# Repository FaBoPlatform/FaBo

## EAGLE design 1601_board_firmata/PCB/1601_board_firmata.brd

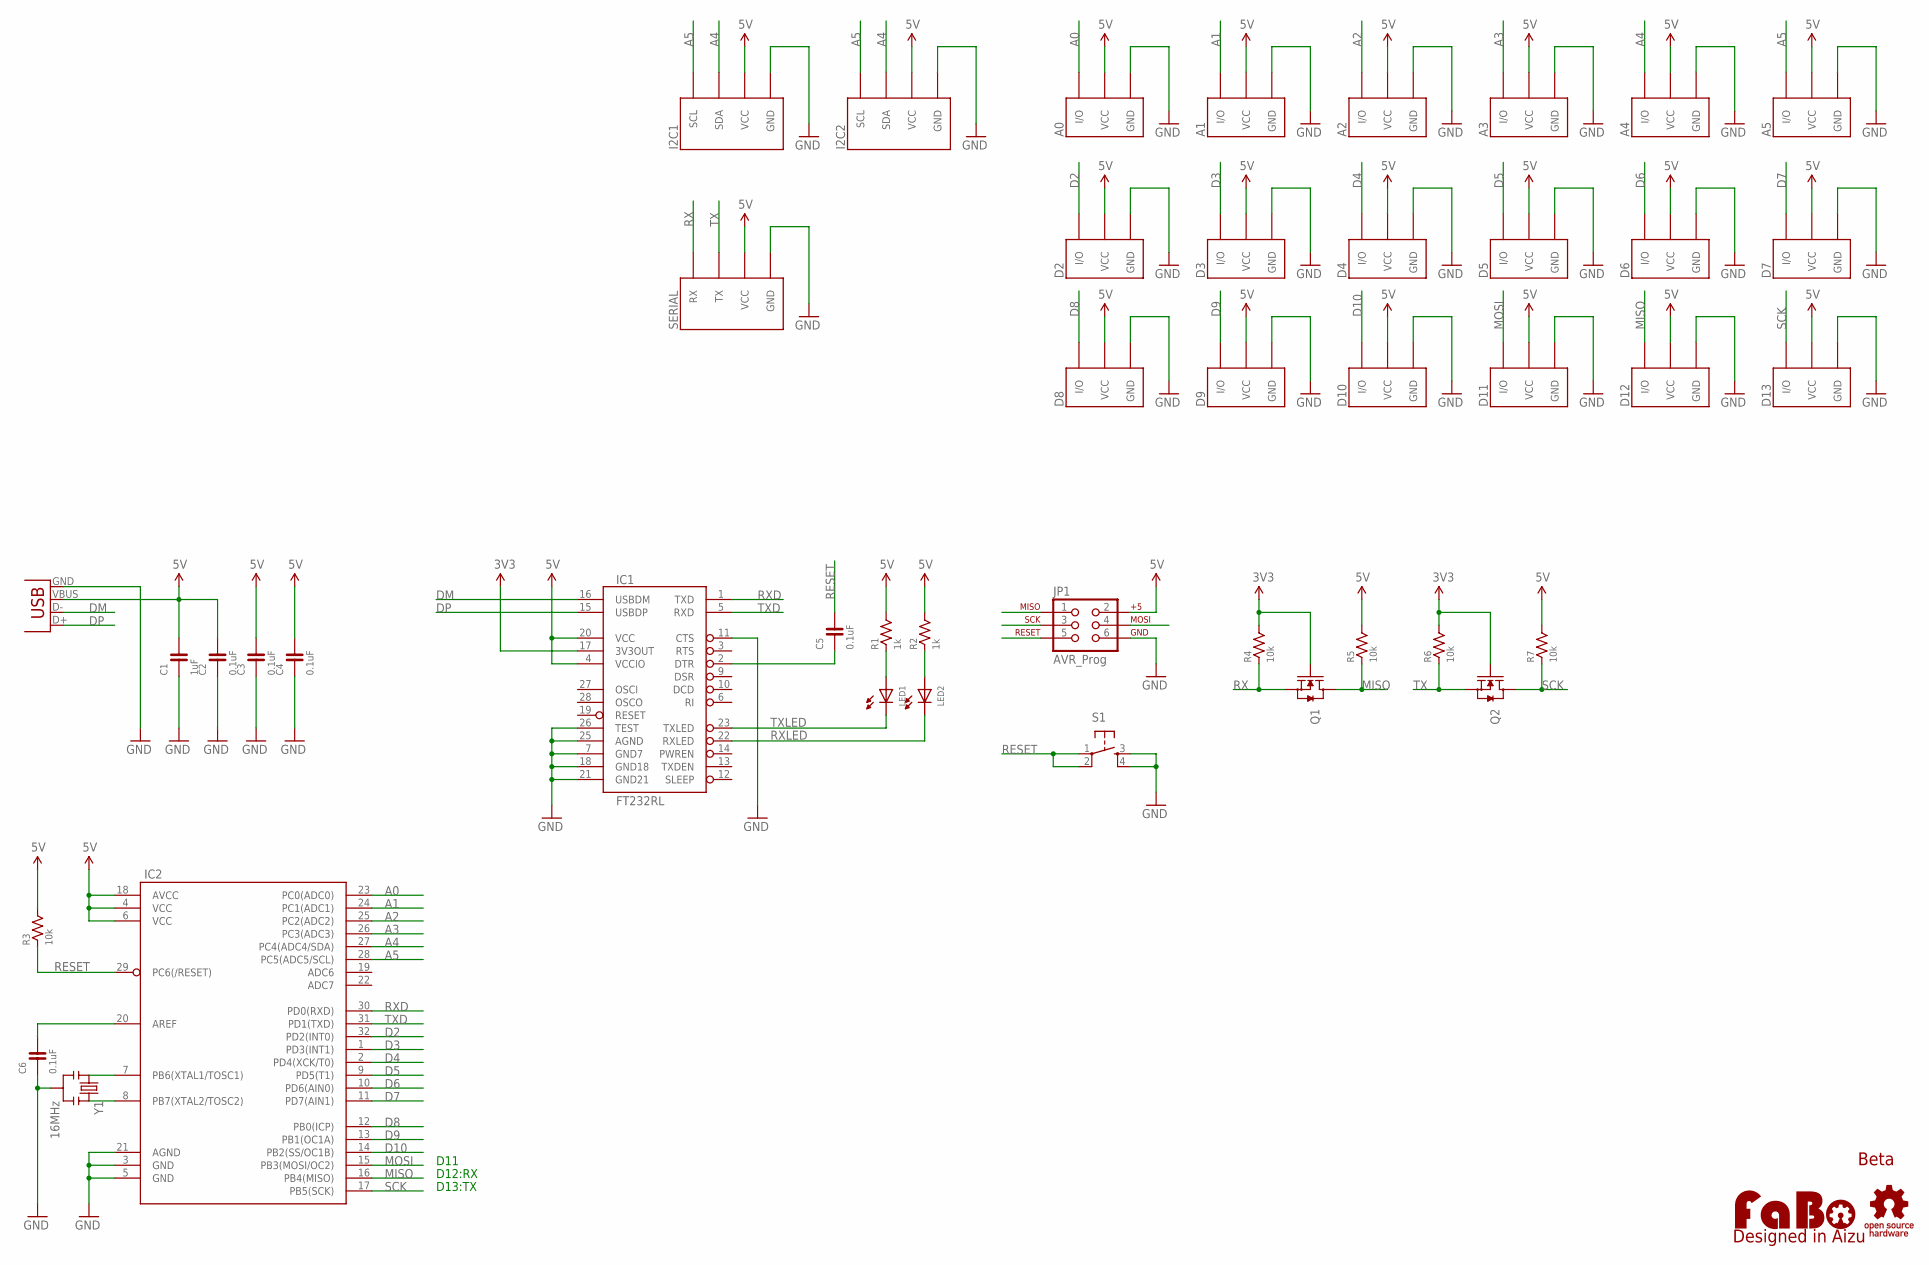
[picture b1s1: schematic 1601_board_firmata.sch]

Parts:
A0, A1, A2, A3, A4, A5: FABO_BRICK_3PIN-S03B-PASK-2; FABO_BRICK_3PIN_S03B-PASK-2
C1: 1uF; 0603
C2, C3, C4, C5, C6: 0.1uF; 0603
D2, D3, D4, D5, D6, D7, D8, D9, D10, D11, D12, D13: FABO_BRICK_3PIN-B03B-PASK-1; FABO_BRICK_3PIN_B03B-PASK-1
I2C1, I2C2: FABO_BRICK_I2C-S04B-PASK-2; FABO_BRICK_I2C_S04B-PASK-2
IC1: FT232RL; SSOP28
IC2: ATMEGA328P-AU-TQFP32; TQFP-32-08
JP1: AVR_Prog; TC2030-MCP
LED1, LED2: LED-0603; 0603
Q1, Q2: MOSFET-N-BSS138; SOT23-3
R1, R2: 1k; 0603
R3, R4, R5, R6, R7: 10k; 0603
S1: TACT-SWITCH-SMD_KMR2; KMR2
SERIAL: FABO_BRICK_SERIAL-S04B-PASK-2; FABO_BRICK_SERIAL_S04B-PASK-2
U$2: LOGO_OSHW-T_M_BOTTOM; LOGO_OSHW_T_MS_BOTTOM
U$3: LOGO_FABO-M; LOGO_FABO_MS
USB1: USB-B-MICRO_SMD; USB_B_MICRO
Y1: 16MHz; RESONATOR_SMD

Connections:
3V3: IC1.17 (3V3OUT), Q1.1 (G), Q2.1 (G), R4.2, R6.2
5V: A0.VCC, A1.VCC, A2.VCC, A3.VCC, A4.VCC, A5.VCC, C1.2, C2.2, C3.2, C4.2, D2.VCC, D3.VCC, D4.VCC, D5.VCC, D6.VCC, D7.VCC, D8.VCC, D9.VCC, D10.VCC, D11.VCC, D12.VCC, D13.VCC, I2C1.VCC, I2C2.VCC, IC1.4 (VCCIO), IC1.20 (VCC), IC2.4 (VCC), IC2.6 (VCC), IC2.18 (AVCC), JP1.2, R1.2, R2.2, R3.2, R5.2, R7.2, SERIAL.VCC, USB1.VBUS
A0: A0.I/O, IC2.23 (PC0(ADC0))
A1: A1.I/O, IC2.24 (PC1(ADC1))
A2: A2.I/O, IC2.25 (PC2(ADC2))
A3: A3.I/O, IC2.26 (PC3(ADC3))
A4: A4.I/O, I2C1.SDA, I2C2.SDA, IC2.27 (PC4(ADC4/SDA))
A5: A5.I/O, I2C1.SCL, I2C2.SCL, IC2.28 (PC5(ADC5/SCL))
D2: D2.I/O, IC2.32 (PD2(INT0))
D3: D3.I/O, IC2.1 (PD3(INT1))
D4: D4.I/O, IC2.2 (PD4(XCK/T0))
D5: D5.I/O, IC2.9 (PD5(T1))
D6: D6.I/O, IC2.10 (PD6(AIN0))
D7: D7.I/O, IC2.11 (PD7(AIN1))
D8: D8.I/O, IC2.12 (PB0(ICP))
D9: D9.I/O, IC2.13 (PB1(OC1A))
D10: D10.I/O, IC2.14 (PB2(SS/OC1B))
DM: IC1.16 (USBDM), USB1.D-
DP: IC1.15 (USBDP), USB1.D+
DTR: C5.1, IC1.2 (DTR)
GND: A0.GND, A1.GND, A2.GND, A3.GND, A4.GND, A5.GND, C1.1, C2.1, C3.1, C4.1, C6.1, D2.GND, D3.GND, D4.GND, D5.GND, D6.GND, D7.GND, D8.GND, D9.GND, D10.GND, D11.GND, D12.GND, D13.GND, I2C1.GND, I2C2.GND, IC1.7 (GND7), IC1.11 (CTS), IC1.18 (GND18), IC1.21 (GND21), IC1.25 (AGND), IC1.26 (TEST), IC2.3 (GND), IC2.5 (GND), IC2.21 (AGND), JP1.6, S1.3, S1.4, SERIAL.GND, USB1.GND, Y1.2
MISO: D12.I/O, IC2.16 (PB4(MISO)), JP1.1, Q1.3 (D), R5.1
MOSI: D11.I/O, IC2.15 (PB3(MOSI/OC2)), JP1.4
unnamed: LED1.ANODE, R1.1
unnamed: C6.2, IC2.20 (AREF)
unnamed: IC2.8 (PB7(XTAL2/TOSC2)), Y1.3
unnamed: IC2.7 (PB6(XTAL1/TOSC1)), Y1.1
unnamed: LED2.ANODE, R2.1
RESET: C5.2, IC2.29 (PC6(/RESET)), JP1.5, R3.1, S1.1, S1.2
RX: Q1.2 (S), R4.1, SERIAL.RX
RXD: IC1.1 (TXD), IC2.30 (PD0(RXD))
RXLED: IC1.22 (RXLED), LED2.CATHODE
SCK: D13.I/O, IC2.17 (PB5(SCK)), JP1.3, Q2.3 (D), R7.1
TX: Q2.2 (S), R6.1, SERIAL.TX
TXD: IC1.5 (RXD), IC2.31 (PD1(TXD))
TXLED: IC1.23 (TXLED), LED1.CATHODE

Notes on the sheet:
Beta
D11
D12:RX
D13:TX

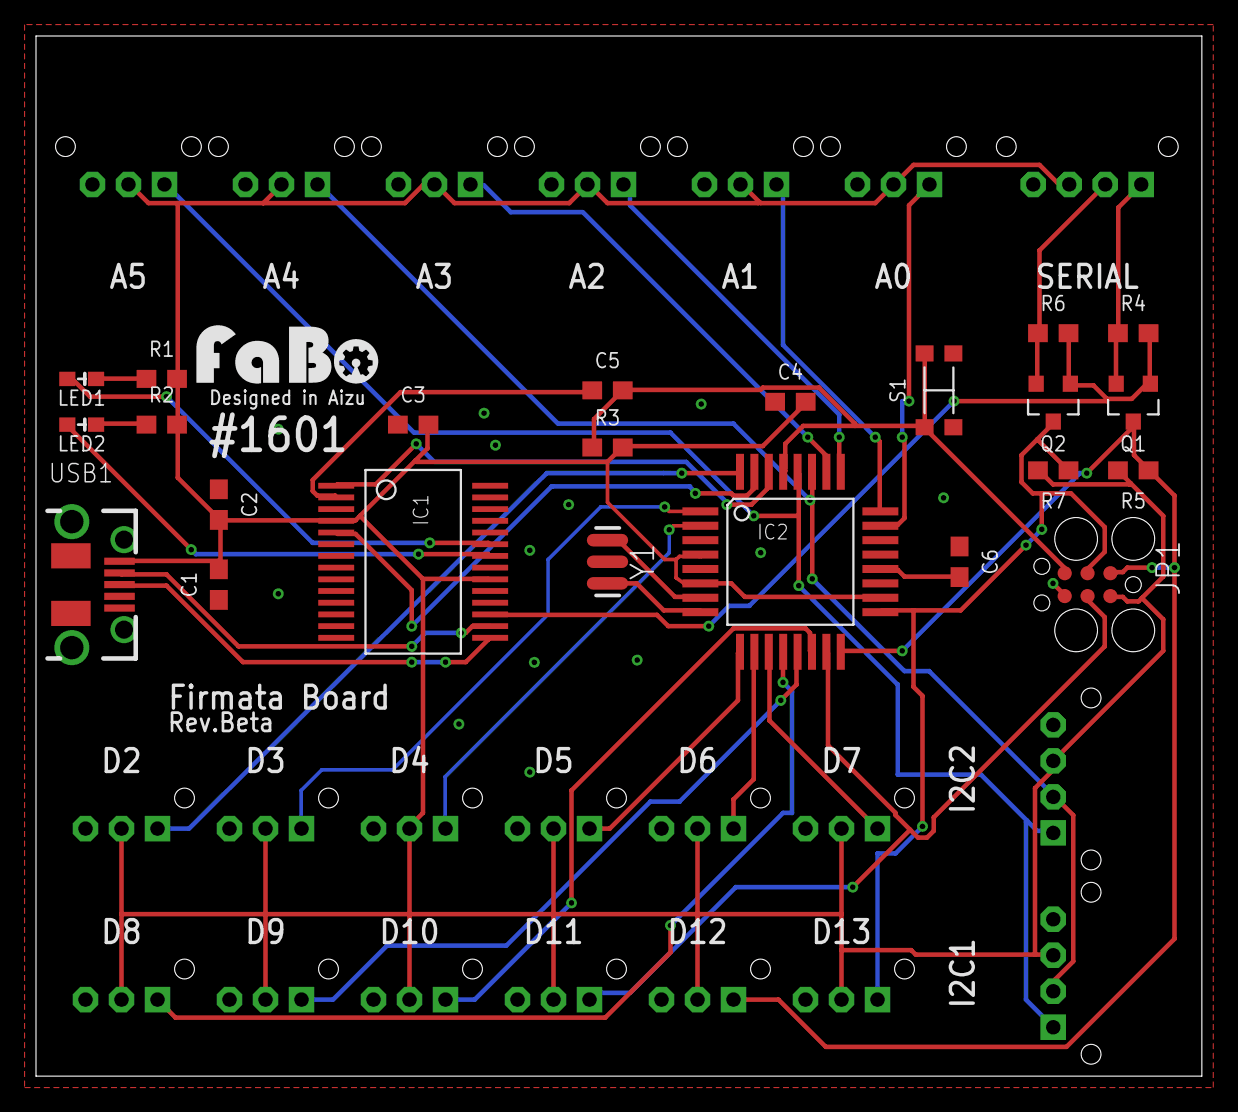
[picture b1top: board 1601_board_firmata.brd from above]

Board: 2 copper layers, 64.8 x 57.8 mm, 46 parts (0 on the bottom side), 36 nets.

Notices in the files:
parts and their libraries:
FaBo-Capacitor: Released under the Creative Commons Attribution-ShareAlike 4.0 License
https://creativecommons.org/licenses/by-sa/4.0
FaBo-etc: Released under the Creative Commons
